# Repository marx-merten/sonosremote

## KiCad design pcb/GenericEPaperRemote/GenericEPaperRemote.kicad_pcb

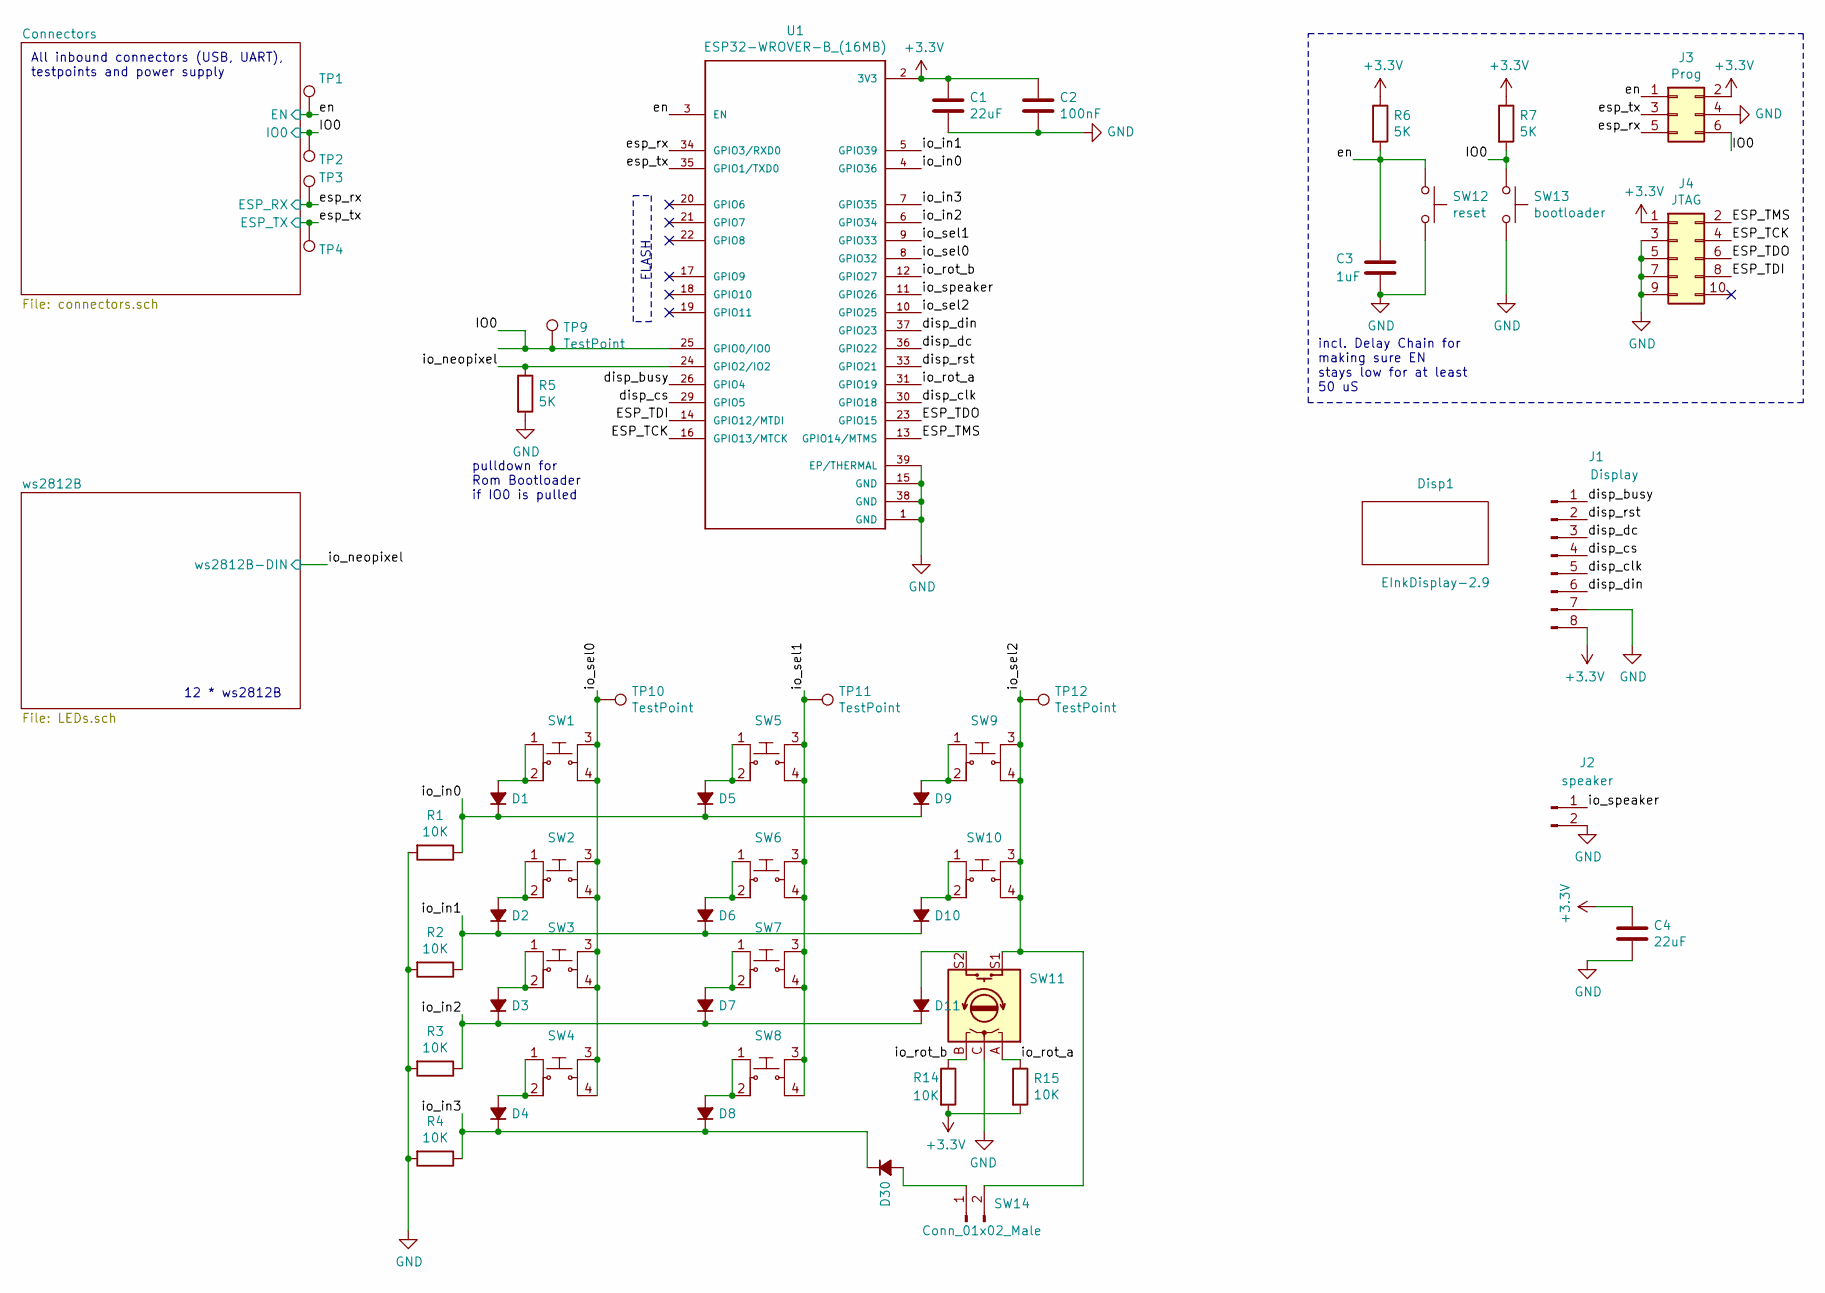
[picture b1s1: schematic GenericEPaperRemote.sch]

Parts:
C1, C4: 22uF; C_1206_3216Metric_Pad1.42x1.75mm_HandSolder; MPN CL31A226MOCLNNC
C2: 100nF; C_0805_2012Metric_Pad1.15x1.40mm_HandSolder; MPN CL21F104ZBCNNNC
C3: 1uF; C_0805_2012Metric_Pad1.15x1.40mm_HandSolder; MPN CL21B105KBFNNNE
D1, D2, D3, D4, D5, D6, D7, D8, D9, D10, D11, D30: D_Small_ALT; D_SOT-23_ANK; MPN BAV99-7-F
Disp1: EInkDisplay-2.9; EInkDisplay2.9
J1: Display; JST_PH_S8B-PH-SM4-TB_1x08-1MP_P2.00mm_Horizontal
J2: speaker; PinHeader_1x02_P2.54mm_Horizontal
J3: Prog; IDC-Header_2x03_P2.54mm_Vertical; MPN C11214
J4: JTAG; IDC-Header_2x05_P2.54mm_Vertical; MPN C5665
R1, R2, R3, R4, R14, R15: 10K; R_0805_2012Metric_Pad1.15x1.40mm_HandSolder
R5, R6, R7: 5K; R_0805_2012Metric_Pad1.15x1.40mm_HandSolder
SW1, SW2, SW3, SW4, SW5, SW6, SW7, SW8, SW9, SW10: TactileSwitchSMD6x6; Switch_Tactile_SMD_6x6mm; MPN 1TS005F-2500-5001
SW11: Rotary_Encoder_Switch; RotaryEncoder_Alps_EC11E-Switch_Vertical_H20mm
SW12: reset; SW_Push_SPST_NO_Alps_SKRK
SW13: bootloader; SW_Push_SPST_NO_Alps_SKRK
SW14: Conn_01x02_Male; PinHeader_1x02_P2.54mm_Vertical
TP1, TP2, TP3, TP4, TP9, TP10, TP11, TP12: TestPoint; TestPoint_THTPad_2.0x2.0mm_Drill1.0mm
U1: ESP32-WROVER-B_(16MB); XCVR_ESP32-WROVER-B_(16MB)

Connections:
+3V3: C1.1, C2.1, C4.1, J1.8, J3.2, J4.1, R6.1, R7.1, R14.2, R15.2, U1.2 (3V3); also elsewhere on the board
/ESP_TCK: J4.4, U1.16 (GPIO13/MTCK)
/ESP_TDI: J4.8, U1.14 (GPIO12/MTDI)
/ESP_TDO: J4.6, U1.23 (GPIO15)
/ESP_TMS: J4.2, U1.13 (GPIO14/MTMS)
/IO0: J3.6, R7.2, SW13.1, TP2.1, TP9.1, U1.25 (GPIO0/IO0); also elsewhere on the board
/disp_busy: J1.1, U1.26 (GPIO4)
/disp_clk: J1.5, U1.30 (GPIO18)
/disp_cs: J1.4, U1.29 (GPIO5)
/disp_dc: J1.3, U1.36 (GPIO22)
/disp_din: J1.6, U1.37 (GPIO23)
/disp_rst: J1.2, U1.33 (GPIO21)
/en: C3.1, J3.1, R6.2, SW12.1, TP1.1, U1.3 (EN); also elsewhere on the board
/esp_rx: J3.5, TP3.1, U1.34 (GPIO3/RXD0); also elsewhere on the board
/esp_tx: J3.3, TP4.1, U1.35 (GPIO1/TXD0); also elsewhere on the board
/io_in0: D1.1 (K), D5.1 (K), D9.1 (K), R1.1, U1.4 (GPIO36)
/io_in1: D2.1 (K), D6.1 (K), D10.1 (K), R2.1, U1.5 (GPIO39)
/io_in2: D3.1 (K), D7.1 (K), D11.1 (K), R3.1, U1.6 (GPIO34)
/io_in3: D4.1 (K), D8.1 (K), D30.1 (K), R4.1, U1.7 (GPIO35)
/io_neopixel: R5.1, U1.24 (GPIO2/IO2); also elsewhere on the board
/io_rot_a: R15.1, SW11.A, U1.31 (GPIO19)
/io_rot_b: R14.1, SW11.B, U1.12 (GPIO27)
/io_sel0: SW1.3, SW1.4, SW2.3, SW2.4, SW3.3, SW3.4, SW4.3, SW4.4, TP10.1, U1.8 (GPIO32)
/io_sel1: SW5.3, SW5.4, SW6.3, SW6.4, SW7.3, SW7.4, SW8.3, SW8.4, TP11.1, U1.9 (GPIO33)
/io_sel2: SW9.3, SW9.4, SW10.3, SW10.4, SW11.S1, SW14.2, TP12.1, U1.10 (GPIO25)
/io_speaker: J2.1, U1.11 (GPIO26)
GND: C1.2, C2.2, C3.2, C4.2, J1.7, J2.2, J3.4, J4.3, J4.5, J4.7, J4.9, R1.2, R2.2, R3.2, R4.2, R5.2, SW11.C, SW12.2, SW13.2, U1.1 (GND), U1.15 (GND), U1.38 (GND), U1.39 (EP/THERMAL); also elsewhere on the board
unnamed: D1.2 (A), SW1.1, SW1.2
unnamed: D2.2 (A), SW2.1, SW2.2
unnamed: D3.2 (A), SW3.1, SW3.2
unnamed: D4.2 (A), SW4.1, SW4.2
unnamed: D5.2 (A), SW5.1, SW5.2
unnamed: D6.2 (A), SW6.1, SW6.2
unnamed: D7.2 (A), SW7.1, SW7.2
unnamed: D8.2 (A), SW8.1, SW8.2
unnamed: D9.2 (A), SW9.1, SW9.2
unnamed: D10.2 (A), SW10.1, SW10.2
unnamed: D11.2 (A), SW11.S2
unnamed: D30.2 (A), SW14.1

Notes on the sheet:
All inbound connectors (USB, UART), testpoints and power supply
incl. Delay Chain for making sure EN stays low for at least 50 uS
pulldown for Rom Bootloader if IO0 is pulled
FLASH
12 * ws2812B

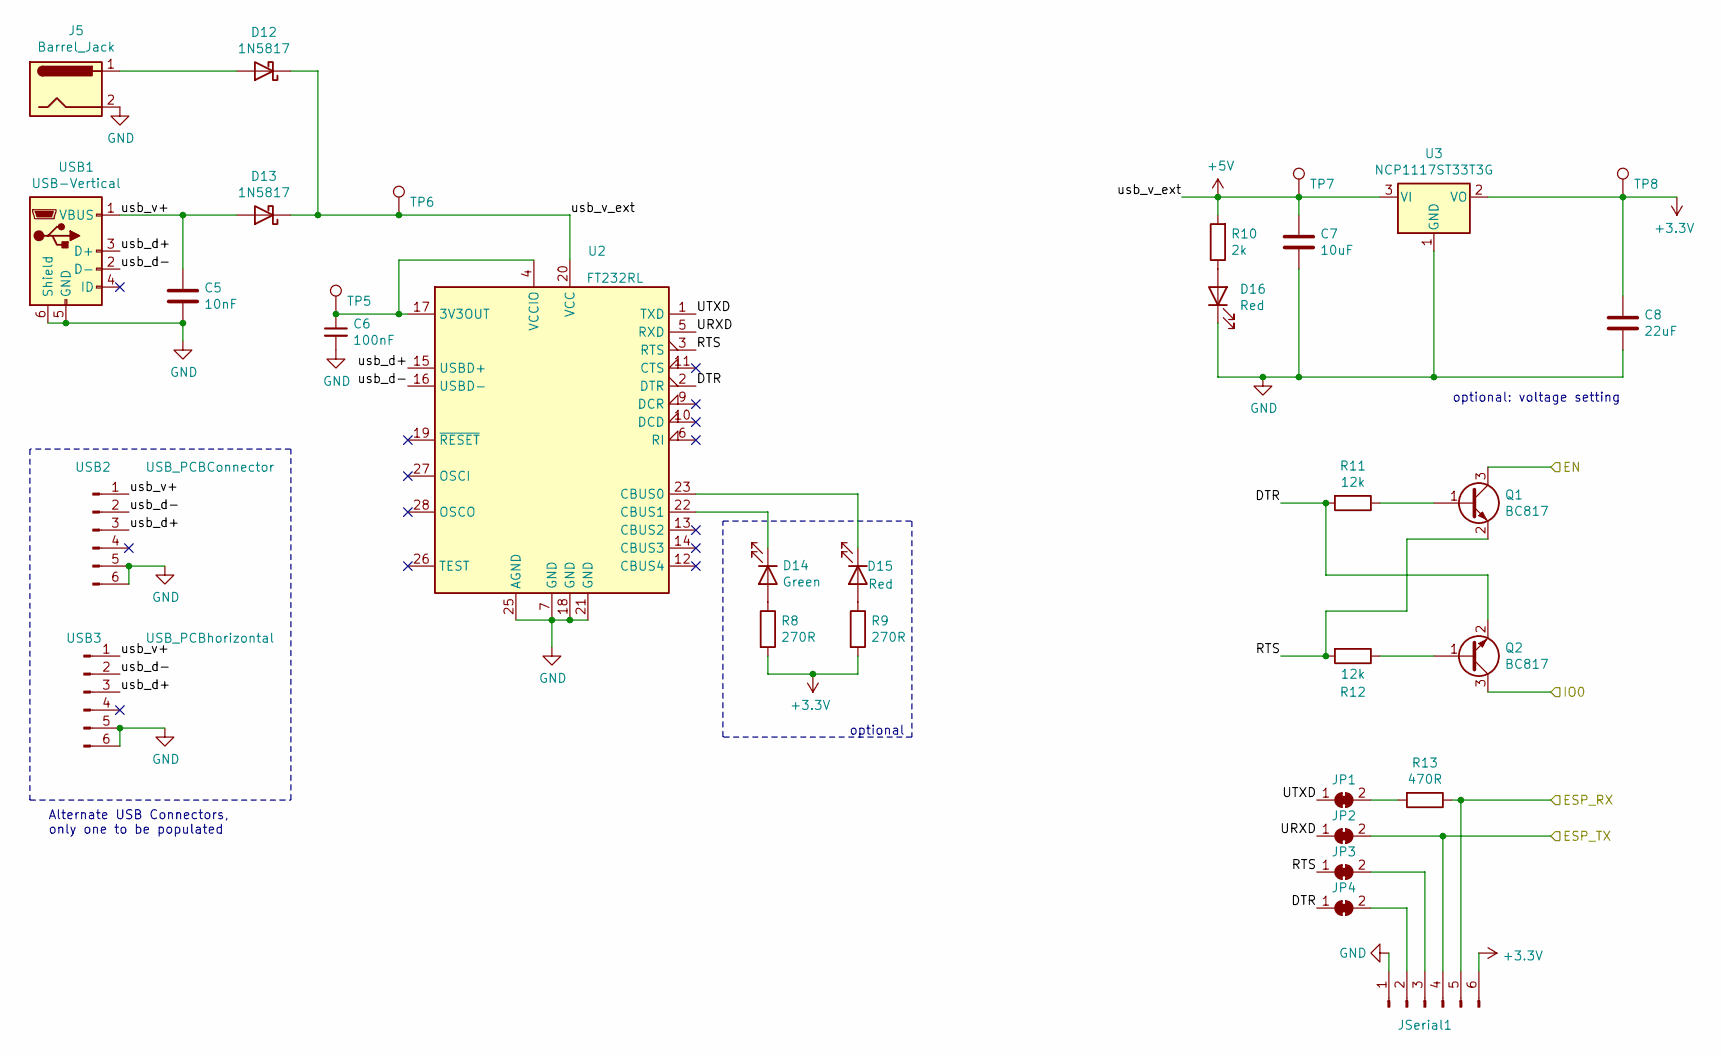
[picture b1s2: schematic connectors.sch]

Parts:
C5: 10nF; C_0805_2012Metric_Pad1.15x1.40mm_HandSolder; MPN CL21B103KBCNNNC
C6: 100nF; C_0805_2012Metric_Pad1.15x1.40mm_HandSolder; MPN CL21F104ZBCNNNC
C7: 10uF; C_1206_3216Metric_Pad1.42x1.75mm_HandSolder; MPN CL31F106ZPENNNE
C8: 22uF; C_1206_3216Metric_Pad1.42x1.75mm_HandSolder; MPN CL31A226MOCLNNC
D12, D13: 1N5817; D_SMB_Handsoldering
D14: Green; LED_1206_3216Metric_Pad1.42x1.75mm_HandSolder; MPN TJ-S3216SW9TGLC2G-A5
D15, D16: Red; LED_1206_3216Metric_Pad1.42x1.75mm_HandSolder; MPN TJ-S3216SW9TGLC2R-A5
J5: Barrel_Jack; BarrelJack_CUI_PJ-063AH_Horizontal
JP1, JP2, JP3, JP4: SolderJumper_2_Bridged; SolderJumper-2_P1.3mm_Bridged_RoundedPad1.0x1.5mm
JSerial1: Conn_01x06_Male; PinHeader_1x06_P2.54mm_Horizontal; MPN PZ254R-11-06P
Q1, Q2: BC817; SOT-23; MPN BC817-25LT1G
R8, R9: 270R; R_0805_2012Metric_Pad1.15x1.40mm_HandSolder
R10: 2k; R_0805_2012Metric_Pad1.15x1.40mm_HandSolder
R11, R12: 12k; R_0805_2012Metric_Pad1.15x1.40mm_HandSolder
R13: 470R; R_0805_2012Metric_Pad1.15x1.40mm_HandSolder
TP5, TP6, TP7, TP8: TestPoint; TestPoint_THTPad_2.0x2.0mm_Drill1.0mm
U2: FT232RL; SSOP-28_5.3x10.2mm_P0.65mm
U3: NCP1117ST33T3G; SOT-223-3_TabPin2; MPN NCP1117ST33T3G
USB1: USB-Vertical; USB_Micro-B_Molex-105133-0031
USB2: USB_PCBConnector; PinHeader_1x06_P2.54mm_Vertical
USB3: USB_PCBhorizontal; USB_Micro-B_Molex_47346-0001

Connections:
+3V3: C8.1, JSerial1.6, R8.2, R9.2, TP8.1, U3.2 (VO); also elsewhere on the board
+5V: C7.1, D12.1 (K), D13.1 (K), R10.2, TP6.1, TP7.1, U2.20 (VCC), U3.3 (VI); also elsewhere on the board
/Connectors/DTR: JP4.1 (A), Q2.2 (E), R11.2, U2.2 (DTR)
/Connectors/RTS: JP3.1 (A), Q1.2 (E), R12.2, U2.3 (RTS)
/Connectors/URXD: JP2.1 (A), U2.5 (RXD)
/Connectors/UTXD: JP1.1 (A), U2.1 (TXD)
/Connectors/usb_d+: U2.15 (USBD+), USB1.3 (D+), USB2.3, USB3.3
/Connectors/usb_d-: U2.16 (USBD-), USB1.2 (D-), USB2.2, USB3.2
/Connectors/usb_v+: C5.1, D13.2 (A), USB1.1 (VBUS), USB2.1, USB3.1
/IO0: Q2.3 (C); also elsewhere on the board
/en: Q1.3 (C); also elsewhere on the board
/esp_rx: JSerial1.5, R13.1; also elsewhere on the board
/esp_tx: JP2.2 (B), JSerial1.4; also elsewhere on the board
GND: C5.2, C6.2, C7.2, C8.2, D16.1 (K), J5.2, JSerial1.1, U2.7 (GND), U2.18 (GND), U2.21 (GND), U2.25 (AGND), U3.1 (GND), USB1.5 (GND), USB1.6 (Shield), USB2.5, USB2.6, USB3.5, USB3.6; also elsewhere on the board
unnamed: C6.1, TP5.1, U2.4 (VCCIO), U2.17 (3V3OUT)
unnamed: D12.2 (A), J5.1
unnamed: D14.1 (K), U2.22 (CBUS1)
unnamed: D14.2 (A), R8.1
unnamed: D15.1 (K), U2.23 (CBUS0)
unnamed: D15.2 (A), R9.1
unnamed: D16.2 (A), R10.1
unnamed: JP1.2 (B), R13.2
unnamed: JP3.2 (B), JSerial1.3
unnamed: JP4.2 (B), JSerial1.2
unnamed: Q1.1 (B), R11.1
unnamed: Q2.1 (B), R12.1

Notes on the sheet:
Alternate USB Connectors, only one to be populated
optional
optional: voltage setting

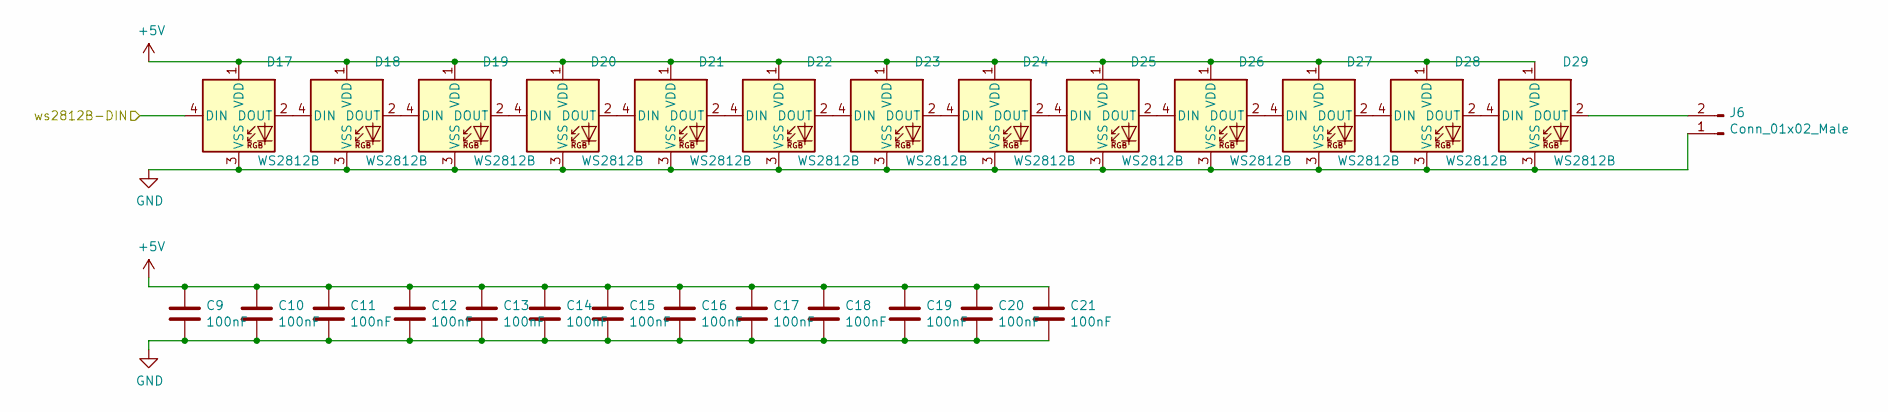
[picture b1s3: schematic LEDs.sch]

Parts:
C9, C10, C11, C12, C13, C14, C15, C16, C17, C18, C19, C20, C21: 100nF; C_0805_2012Metric_Pad1.15x1.40mm_HandSolder; MPN CL21F104ZBCNNNC
D17, D18, D19, D20, D21, D22, D23, D24, D25, D26, D27, D28, D29: WS2812B; LED_WS2812B_PLCC4_5.0x5.0mm_P3.2mm; MPN WS2812B-B
J6: Conn_01x02_Male; PinHeader_1x02_P2.54mm_Vertical

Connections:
+5V: C9.1, C10.1, C11.1, C12.1, C13.1, C14.1, C15.1, C16.1, C17.1, C18.1, C19.1, C20.1, C21.1, D17.1 (VDD), D18.1 (VDD), D19.1 (VDD), D20.1 (VDD), D21.1 (VDD), D22.1 (VDD), D23.1 (VDD), D24.1 (VDD), D25.1 (VDD), D26.1 (VDD), D27.1 (VDD), D28.1 (VDD), D29.1 (VDD); also elsewhere on the board
/io_neopixel: D17.4 (DIN); also elsewhere on the board
GND: C9.2, C10.2, C11.2, C12.2, C13.2, C14.2, C15.2, C16.2, C17.2, C18.2, C19.2, C20.2, C21.2, D17.3 (VSS), D18.3 (VSS), D19.3 (VSS), D20.3 (VSS), D21.3 (VSS), D22.3 (VSS), D23.3 (VSS), D24.3 (VSS), D25.3 (VSS), D26.3 (VSS), D27.3 (VSS), D28.3 (VSS), D29.3 (VSS), J6.1; also elsewhere on the board
unnamed: D17.2 (DOUT), D18.4 (DIN)
unnamed: D18.2 (DOUT), D19.4 (DIN)
unnamed: D19.2 (DOUT), D20.4 (DIN)
unnamed: D20.2 (DOUT), D21.4 (DIN)
unnamed: D21.2 (DOUT), D22.4 (DIN)
unnamed: D22.2 (DOUT), D23.4 (DIN)
unnamed: D23.2 (DOUT), D24.4 (DIN)
unnamed: D24.2 (DOUT), D25.4 (DIN)
unnamed: D25.2 (DOUT), D26.4 (DIN)
unnamed: D26.2 (DOUT), D27.4 (DIN)
unnamed: D27.2 (DOUT), D28.4 (DIN)
unnamed: D28.2 (DOUT), D29.4 (DIN)
unnamed: D29.2 (DOUT), J6.2

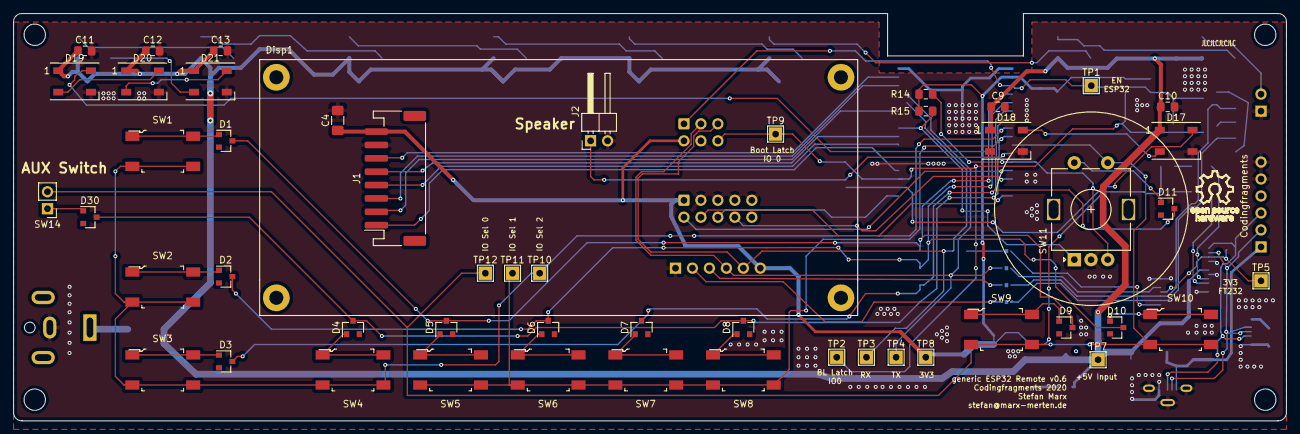
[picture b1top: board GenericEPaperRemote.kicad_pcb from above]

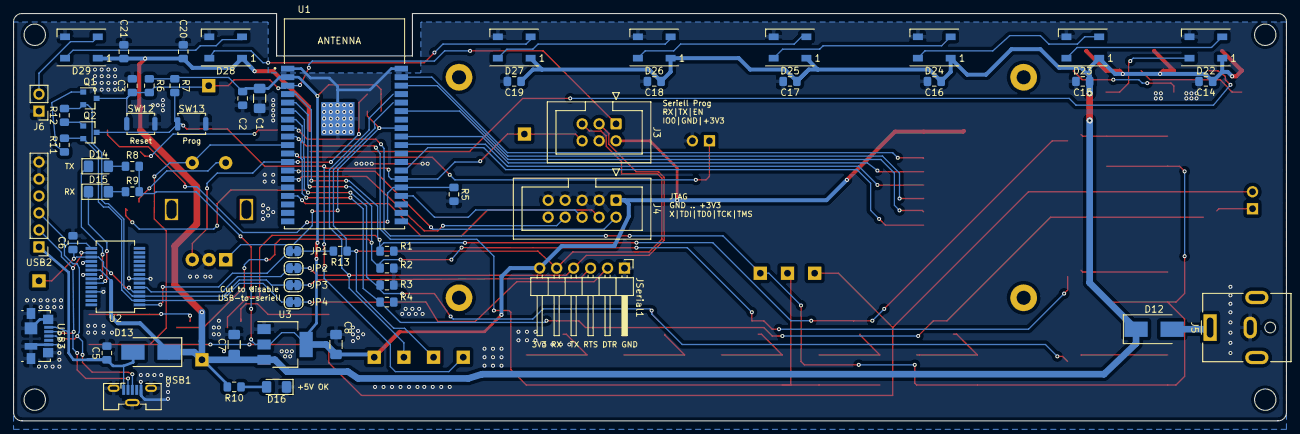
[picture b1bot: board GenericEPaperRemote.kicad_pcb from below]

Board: 2 copper layers, 190.5 x 61.0 mm, 112 parts (60 on the bottom side), 72 nets.

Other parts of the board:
LOGO1: Codingfragments; OSSLogo

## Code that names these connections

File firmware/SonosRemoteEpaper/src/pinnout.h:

// ESP32 nodeMCU 32S
//                                   +------------------------------+
//                          VIN/3V3 -|                              |- GND
//                        RESET--EN -|                [  disp_din  ]|- GPIO23--VPSIMOSI
// (I Only)           ADC0---GPIO36 -| [ in0        ] [ disp_dc    ]|- GPIO22--I2C SCL
// (I Only)           ADC3---GPIO39 -| [ in1        ] [            ]|- GPIO1---TX0
// (I Only)           ADC6---GPIO34 -| [ in2        ] [            ]|- GPIO3---RX0
// (I Only)           ADC7---GPIO35 -| [ in3        ] [ disp_rst   ]|- GPIO21--I2C SDA
//            Touch9--ADC4---GPIO32 -| [ sel0       ]               |- GND
//            Touch8--ADC5---GPIO33 -| [ sel1       ] [            ]|- GPIO19--VSPIMISO
//              DAC1--ADC18--GPIO25 -| [ sel2       ] [ disp_clk   ]|- GPIO18--VSPI/SCK
//              DAC2--ADC19--GPIO26 -| [ speaker    ] [ disp_cs    ]|- GPIO5---VSPI/SS
//            Touch7--ADC17--GPIO27 -| [ rot_b      ] [ *PS-Ram*   ]|- GPIO17--TX1
//  HSPI/CLK--Touch6--ADC16--GPIO14 -| [*jtag*      ] [ *PS-Ram*   ]|- GPIO16--RX1
//  HSPIMISO--Touch5--ADC15--GPIO12 -| [*jtag*      ] [ disp_busy  ]|- GPIO4---ADC10----TOUCH0
//                              GND -| [            ] [ rot_a      ]|- GPIO0---ADC11----TOUCH1
//  HSPIMOSI--Touch4--ADC14--GPIO13 -| [*jtag*      ] [ (neopixel) ]|- GPIO2---ADC12----TOUCH2
//                 FLASH/D2---GPIO9 -| [**reserved**] [ **jtag**   ]|- GPIO15--ADC13----TOUCH3--HSPI/CS
//                 FLASH/D3--GPIO10 -| [**reserved**] [**reserved**]|- GPIO8---FLASH/D1
//                 FLASHCMD--GPIO11 -| [**reserved**] [**reserved**]|- GPIO7---FLASH/D0
//                           VIN/5V -|                [**reserved**]|- GPIO6---FLASHSCK
//                                   +------------+-----+-----------+
//                                      (EN)     | USB |  (Prog)
//                                              +-----+
//<JTAG PINS>

// Used Pins

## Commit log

2020-10-25 initial pcb
2020-10-25 initial firmware tests
2020-10-25 Finalize first version of pcb
2020-10-25 small changes
2020-11-09 Added pullups for encoder and switch away from io0 to prevent boot to root-loader when rotary encoder pulls low)
2020-11-17 added 58g2 fonts
2020-11-17 added tools
2020-11-18 Added ESP32 Board Definition
2020-11-18 Env Config
2020-11-18 Added Stubs local samples dir
2020-11-18 Micropython build config
2020-11-18 Save the work
2020-11-18 Redo-fonts prep
2020-11-18 updated global keycodes
2020-11-18 added globals
2020-11-18 Added epaper driver from MCauser
2020-11-18 graphics, primitice completed
2020-11-18 simplified startscript for unix-port
2020-11-18 esp32 board tests
2020-11-18 modified epaper base module, supports for graphic canvas
2020-11-18 imported from C-library
2020-11-18 cleanup
2020-11-18 allowed window canvas to be cleared, needed for glyph drawing and fast clear
2020-11-18 moved encodings to asciitable and low unicode
2020-11-18 initial draw /string support functional
2020-11-18 autoset fontname in local context
2020-11-21 added rotary encoder setup
2020-11-21 python modules visibillity tests
2020-11-21 basic fonts test
2020-11-21 simple audio buzzer test
2020-11-21 check epd paper support with font caching enabled
2020-11-21 flexible port selection allways use the first ftt32 usbserial port
2020-11-22 better dirty check on syncfs
2020-11-22 split into firmaware and libs
2020-11-22 logging base framework
2020-11-22 allow cmd line arguments
2020-11-30 local md5 should never be in git
2020-11-30 added base led mood support
2020-11-30 add loop() for reentering execution loop and fade out led for status bar
2020-11-30 updated Logging
2020-11-30 support for positive only delta on big integeres that support rollover
2020-11-30 wifi, experiments
2020-11-30 move main reporting to log framework and move led tests to seperate file structure with reentry capable methods
2020-11-30 all local md5 should not be in git history
2020-11-30 enabled optimized rebuild cycle
2020-11-30 moved boot logging to logging framework
2020-11-30 added extension pins for ws2812b
2020-12-23 added aux ws2812B Socket (J6)
2020-12-23 added .DSStore to gitignore
2024-02-16 last changes
